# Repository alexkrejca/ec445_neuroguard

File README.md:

# ec445_neuroguard
Repository for ECE 445 Senior Design Project, Neuroguard

# Lab Notebook
# 10/5

# 10/7

# 10/8
Using the ESU Monitor we created over the past couple days, we completed our first breadboard demo.

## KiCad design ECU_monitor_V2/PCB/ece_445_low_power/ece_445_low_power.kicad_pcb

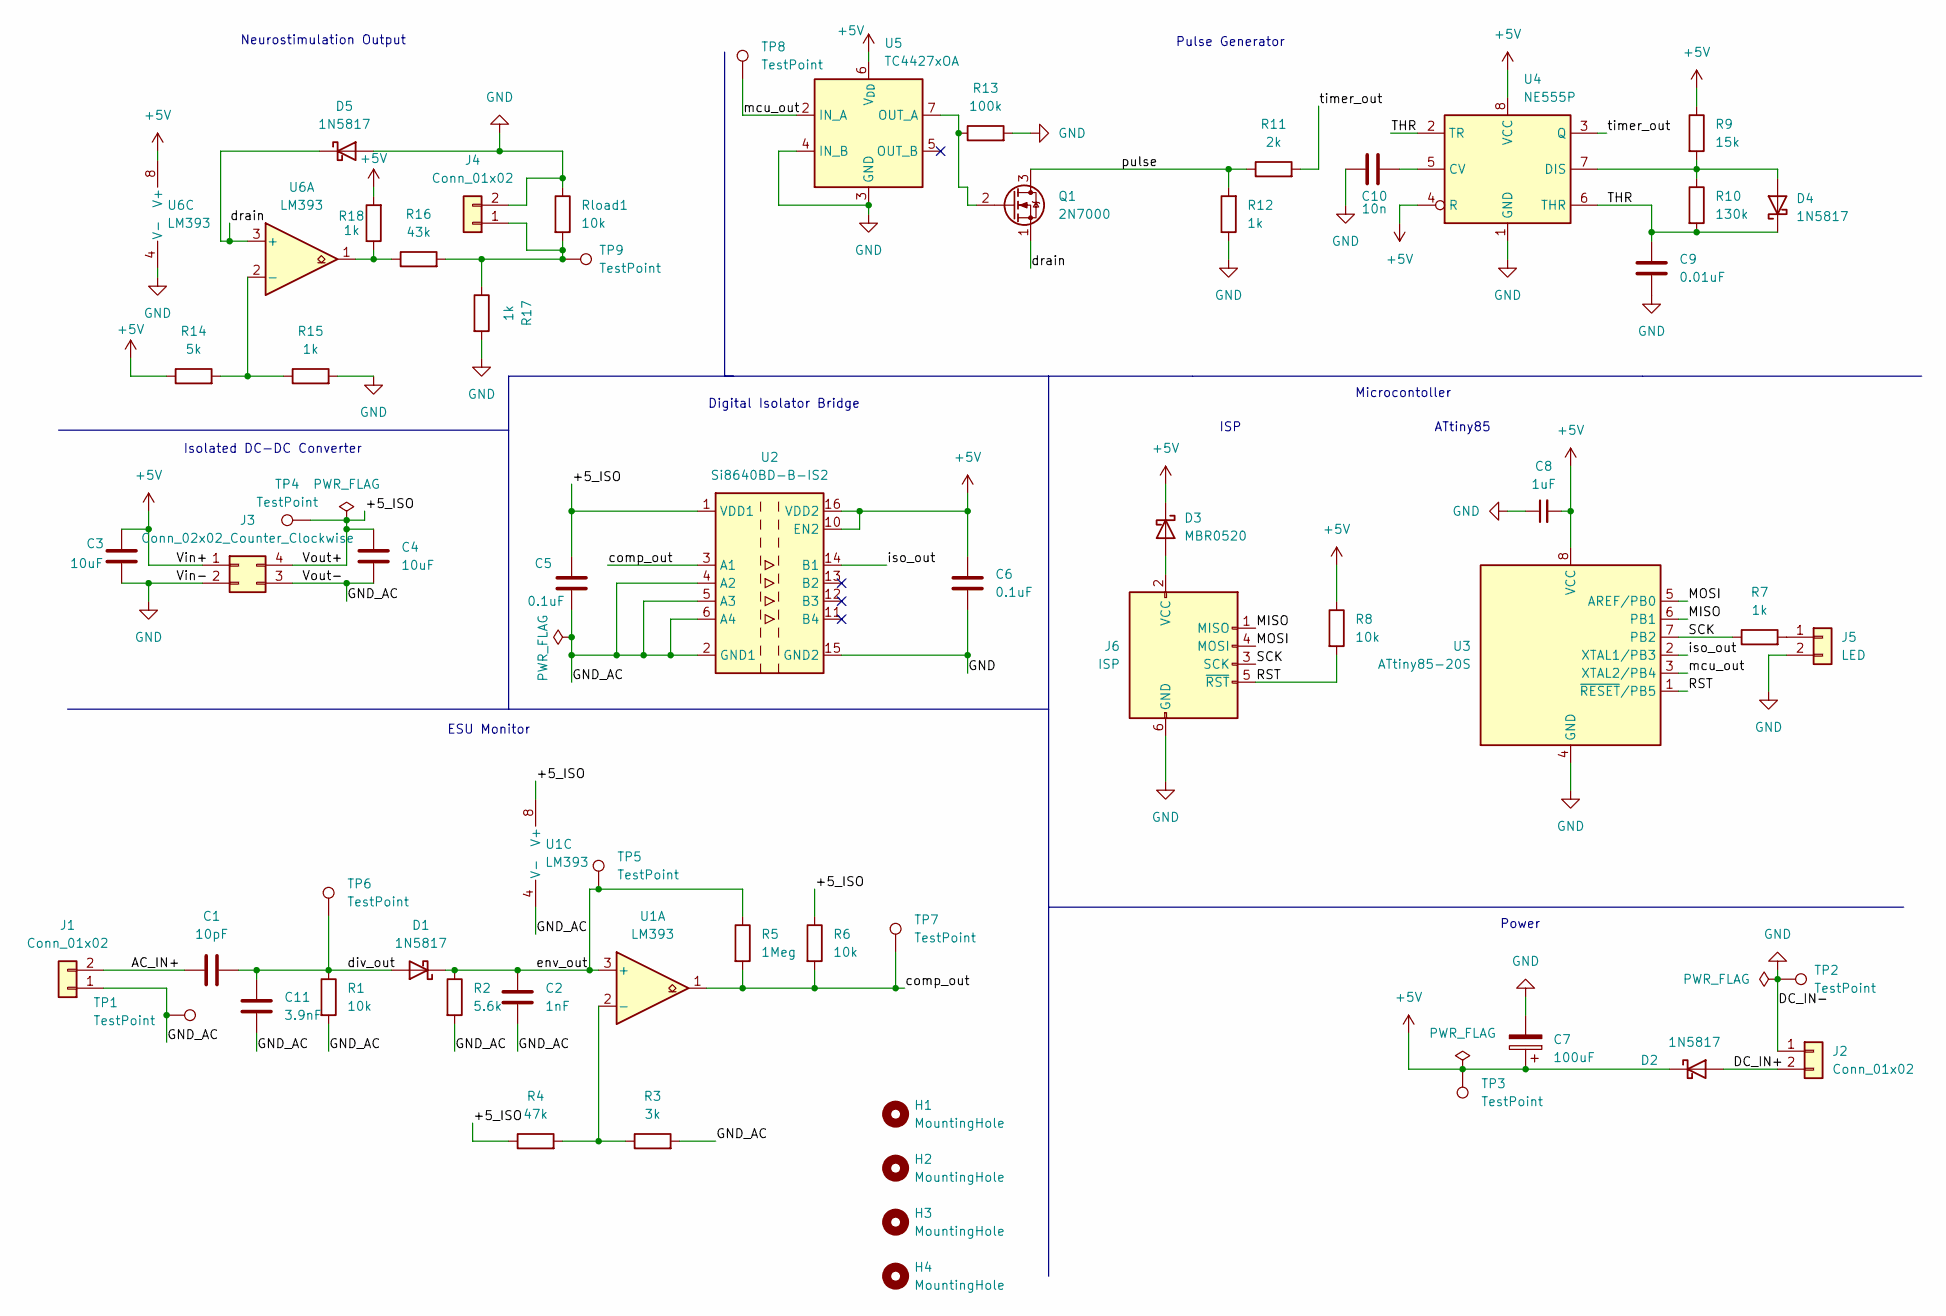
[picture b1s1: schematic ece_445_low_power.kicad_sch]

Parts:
C1: 10pF; C_Disc_D4.7mm_W2.5mm_P5.00mm
C2: 1nF; C_Disc_D4.7mm_W2.5mm_P5.00mm
C3, C4: 10uF; C_Disc_D4.7mm_W2.5mm_P5.00mm
C5, C6: 0.1uF; C_Disc_D4.7mm_W2.5mm_P5.00mm
C7: 100uF; C_Disc_D4.7mm_W2.5mm_P5.00mm
C8: 1uF; C_Disc_D4.7mm_W2.5mm_P5.00mm
C9: 0.01uF; C_Disc_D4.7mm_W2.5mm_P5.00mm
C10: 10n; C_Disc_D4.7mm_W2.5mm_P5.00mm
C11: 3.9nF; C_Disc_D4.7mm_W2.5mm_P5.00mm
D1, D2, D4, D5: 1N5817; D_DO-41_SOD81_P10.16mm_Horizontal
D3: MBR0520; D_SOD-123
H1, H2, H3, H4: MountingHole; MountingHole_3.2mm_M3
J1, J2, J4: Conn_01x02; PinHeader_1x02_P2.54mm_Vertical
J3: Conn_02x02_Counter_Clockwise; PinHeader_1x04_P2.54mm_Vertical
J5: LED; Molex_KK-254_AE-6410-02A_1x02_P2.54mm_Vertical
J6: ISP; IDC-Header_2x03_P2.54mm_Vertical
Q1: 2N7000; TO-92_Inline
R1, R6, R8: 10k; R_Axial_DIN0207_L6.3mm_D2.5mm_P10.16mm_Horizontal
R2: 5.6k; R_Axial_DIN0207_L6.3mm_D2.5mm_P10.16mm_Horizontal
R3: 3k; R_Axial_DIN0207_L6.3mm_D2.5mm_P10.16mm_Horizontal
R4: 47k; R_Axial_DIN0207_L6.3mm_D2.5mm_P10.16mm_Horizontal
R5: 1Meg; R_Axial_DIN0207_L6.3mm_D2.5mm_P10.16mm_Horizontal
R7, R12, R15, R17, R18: 1k; R_Axial_DIN0207_L6.3mm_D2.5mm_P10.16mm_Horizontal
R9: 15k; R_Axial_DIN0207_L6.3mm_D2.5mm_P10.16mm_Horizontal
R10: 130k; R_Axial_DIN0207_L6.3mm_D2.5mm_P10.16mm_Horizontal
R11: 2k; R_Axial_DIN0207_L6.3mm_D2.5mm_P10.16mm_Horizontal
R13: 100k; R_Axial_DIN0207_L6.3mm_D2.5mm_P10.16mm_Horizontal
R14: 5k; R_Axial_DIN0207_L6.3mm_D2.5mm_P10.16mm_Horizontal
R16: 43k; R_Axial_DIN0207_L6.3mm_D2.5mm_P10.16mm_Horizontal
Rload1: 10k; R_Axial_DIN0207_L6.3mm_D2.5mm_P10.16mm_Horizontal
TP1, TP2, TP3, TP4, TP5, TP6, TP7, TP8, TP9: TestPoint; TestPoint_Pad_D1.5mm
U1, U6: LM393; DIP-8_W7.62mm
U2: Si8640BD-B-IS2; SOIC-16W_7.5x10.3mm_P1.27mm
U3: ATtiny85-20S; SOIC-8_5.3x5.3mm_P1.27mm
U4: NE555P; DIP-8_W7.62mm
U5: TC4427xOA; SOIC-8_3.9x4.9mm_P1.27mm

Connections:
+5V: C3.2, C6.1, C7.1, C8.2, D2.1 (K), D3.1 (K), J3.1, R8.1, R9.1, R14.1, R18.2, TP3.1, U2.10 (EN2), U2.16 (VDD2), U3.8 (VCC), U4.4 (R), U4.8 (VCC), U5.6 (V_{DD}), U6.8 (V+)
/+5_ISO: C4.2, C5.1, J3.4, R4.1, R6.1, TP4.1, U1.8 (V+), U2.1 (VDD1)
/AC_IN+: C1.1, J1.2
/DC_IN+: D2.2 (A), J2.2
/GND_AC: C2.2, C4.1, C5.2, C11.1, J1.1, J3.3, R1.2, R2.2, R3.2, TP1.1, U1.4 (V-), U2.2 (GND1), U2.4 (A2), U2.5 (A3), U2.6 (A4), U2.8 (GND1)
/MISO: J6.1 (MISO), U3.6 (PB1)
/MOSI: J6.4 (MOSI), U3.5 (AREF/PB0)
/RST: J6.5 (~RST), R8.2, U3.1 (~RESET/PB5)
/SCK: J6.3 (SCK), R7.1, U3.7 (PB2)
/THR: C9.1, D4.1 (K), R10.2, U4.2 (TR), U4.6 (THR)
/comp_out: R5.2, R6.2, TP7.1, U1.1, U2.3 (A1)
/div_out: C1.2, C11.2, D1.2 (A), R1.1, TP6.1
/drain: D5.1 (K), Q1.1 (S), U6.3 (+)
/env_out: C2.1, D1.1 (K), R2.1, R5.1, TP5.1, U1.3 (+)
/iso_out: U2.14 (B1), U3.2 (XTAL1/PB3)
/mcu_out: TP8.1, U3.3 (XTAL2/PB4), U5.2 (IN_A)
/pulse: Q1.3 (D), R11.1, R12.2
/timer_out: R11.2, U4.3 (Q)
GND: C3.1, C6.2, C7.2, C8.1, C9.2, C10.1, D5.2 (A), J2.1, J3.2, J4.2, J5.2, J6.6 (GND), R12.1, R13.2, R15.2, R17.2, Rload1.1, TP2.1, U2.9 (GND2), U2.15 (GND2), U3.4 (GND), U4.1 (GND), U5.3 (GND), U5.4 (IN_B), U6.4 (V-)
unnamed: D3.2 (A), J6.2 (VCC)
unnamed: D4.2 (A), R9.2, R10.1, U4.7 (DIS)
unnamed: J4.1, R16.2, R17.1, Rload1.2, TP9.1
unnamed: J5.1, R7.2
unnamed: Q1.2 (G), R13.1, U5.7 (OUT_A)
unnamed: R16.1, R18.1, U6.1
unnamed: R3.1, R4.2, U1.2 (-)
unnamed: C10.2, U4.5 (CV)
unnamed: R14.2, R15.1, U6.2 (-)

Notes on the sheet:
ESU Monitor
Pulse Generator
Neurostimulation Output
Digital Isolator Bridge
Isolated DC-DC Converter
Microcontoller
ISP
Power
ATtiny85

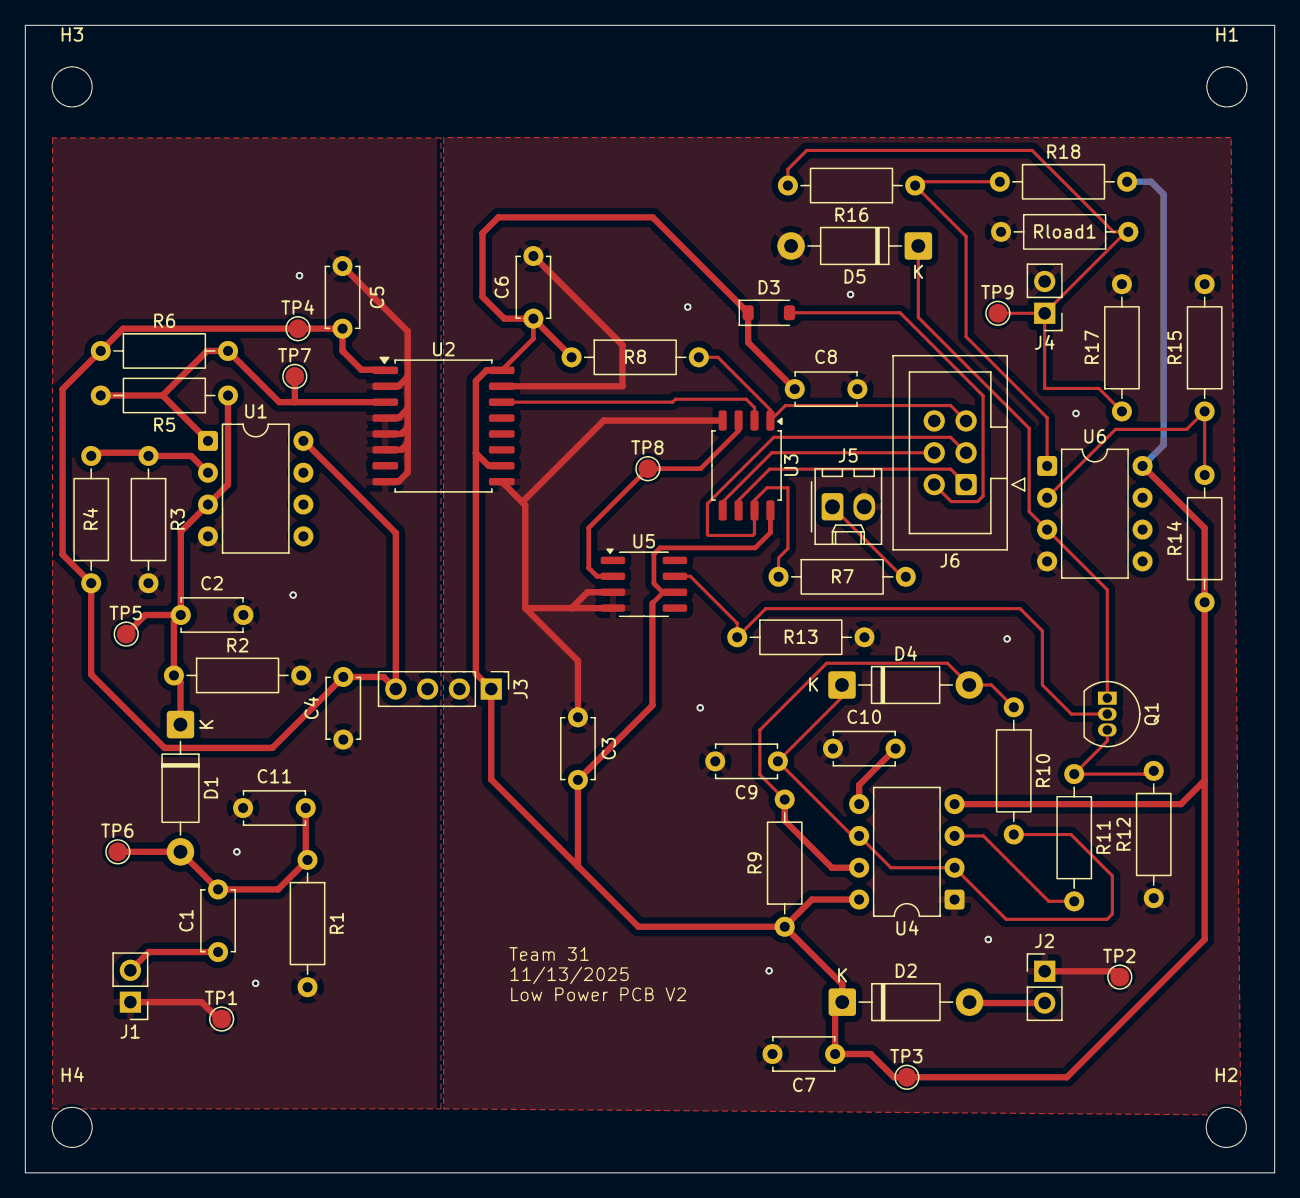
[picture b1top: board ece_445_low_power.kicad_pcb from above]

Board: 2 copper layers, 99.7 x 91.6 mm, 61 parts (0 on the bottom side), 28 nets.

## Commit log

2025-09-22 Neuroguard_project_proposal
2025-09-22 Create thing
2025-10-08 Adding ECU_monitor
2025-10-08 Adding Power folder
2025-10-08 move documents to their own folder
2025-10-08 Adding images from Breadboard
2025-10-13 better design ESU monitor
2025-10-13 Include nerve stimulation circuit with mosfet
2025-10-17 Adding low_power pcb
2025-10-26 Adding Breadboard Pictures
2025-11-20 Adding stripped PCB to github
2025-12-09 Add README.md for Aidan Moran's laboratory notebook
2025-12-09 Create gitmaintain
2025-12-10 Revise README with recent project updates
    Updated README.md with additional meeting notes and project details.
2025-12-10 Adding stephen notebook
2025-12-10 formating notebook
2025-12-10 Removing unwanted files
2025-12-11 Create Alex Krejca
2025-12-11 Update README with new references and meeting notes
    Added references and updated meeting notes in README.
2025-12-11 Document testing integration with low voltage stage
    Added a section on testing integration with the low voltage stage, detailing the setup and observations during testing.
2025-12-12 Update README.md from lab manual
2025-12-12 Fixed Formatting Errors
2025-12-12 Fix again?
2026-01-11 Updated Low Power PCB, added missing 1k resistor to +5V in output
2026-01-11 Adding Final Report to github
2026-01-11 cleanup of ECUMonitor to remove extra wires
